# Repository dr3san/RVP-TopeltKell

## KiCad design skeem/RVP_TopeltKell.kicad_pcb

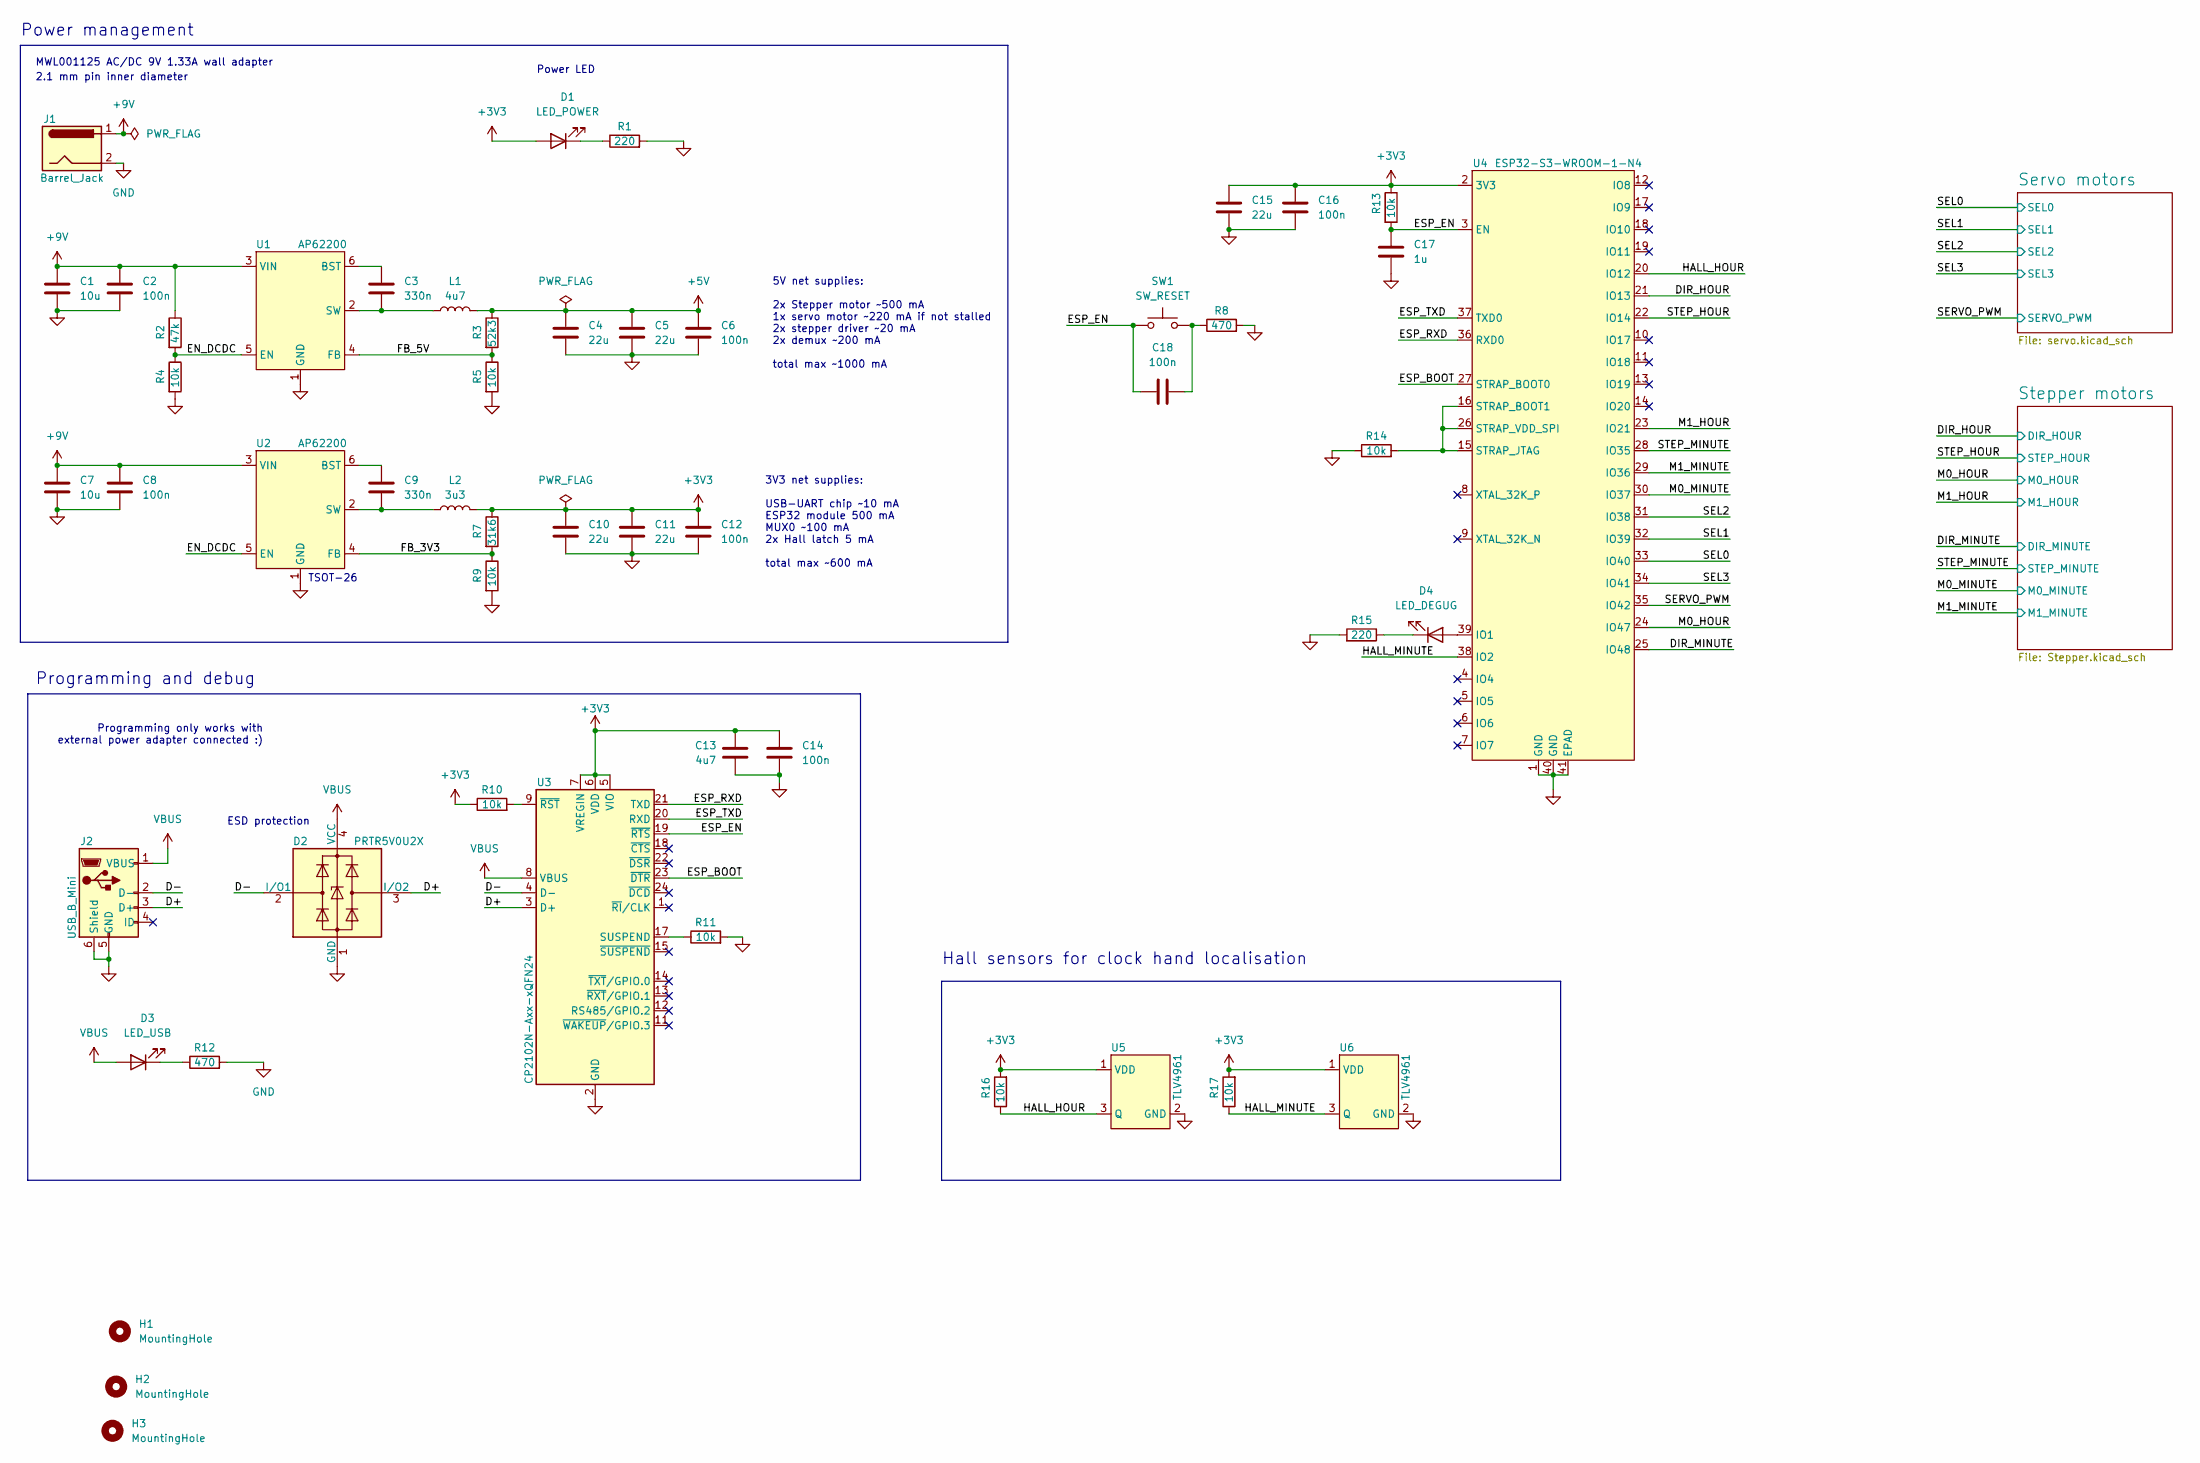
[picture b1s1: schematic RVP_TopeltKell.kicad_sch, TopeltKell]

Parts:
C1, C7: 10u; C_0805_2012Metric_Pad1.18x1.45mm_HandSolder
C2, C6, C8, C12, C14, C16, C18: 100n; C_0603_1608Metric_Pad1.08x0.95mm_HandSolder
C3, C9: 330n; C_0603_1608Metric_Pad1.08x0.95mm_HandSolder
C4, C5, C10, C11, C15: 22u; C_1206_3216Metric_Pad1.33x1.80mm_HandSolder
C13: 4u7; C_0805_2012Metric_Pad1.18x1.45mm_HandSolder
C17: 1u; C_0805_2012Metric_Pad1.18x1.45mm_HandSolder
D1: LED_POWER; LED_0603_1608Metric_Pad1.05x0.95mm_HandSolder
D2: PRTR5V0U2X; SOT-143
D3: LED_USB; LED_0603_1608Metric_Pad1.05x0.95mm_HandSolder
D4: LED_DEGUG; LED_0603_1608Metric_Pad1.05x0.95mm_HandSolder
H1, H2, H3: MountingHole; MountingHole_3.2mm_M3
J1: Barrel_Jack; BarrelJack_CLIFF_FC681465S_SMT_Horizontal
J2: USB_B_Mini; USB_Mini_B
L1: 4u7; L_Wuerth_WE-PD-Typ-7345
L2: 3u3; L_7.3x7.3_H3.5
R1, R15: 220; R_0603_1608Metric_Pad0.98x0.95mm_HandSolder
R2: 47k; R_0603_1608Metric_Pad0.98x0.95mm_HandSolder
R3: 52k3; R_0603_1608Metric_Pad0.98x0.95mm_HandSolder
R4, R5, R9, R10, R11, R13, R14, R16, R17: 10k; R_0603_1608Metric_Pad0.98x0.95mm_HandSolder
R7: 31k6; R_0603_1608Metric_Pad0.98x0.95mm_HandSolder
R8, R12: 470; R_0603_1608Metric_Pad0.98x0.95mm_HandSolder
SW1: SW_RESET; SW_SPST_EVQQ2
U1, U2: AP62200; TSOT26
U3: CP2102N-Axx-xQFN24; QFN-24-1EP_4x4mm_P0.5mm_EP2.6x2.6mm
U4: ESP32-S3-WROOM-1-N4; ESP32-S3-WROOM-1
U5, U6: TLV4961; TO-92S

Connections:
+5V: C4.1, C5.1, C6.2, L1.2, R3.1; also elsewhere on the board
+9V: C1.1, C2.2, C7.1, C8.2, J1.1, R2.1, U1.3 (VIN), U2.3 (VIN); also elsewhere on the board
/D+: D2.3 (I/O2), J2.3 (D+), U3.3 (D+)
/D-: D2.2 (I/O1), J2.2 (D-), U3.4 (D-)
/DIR_HOUR: U4.21 (IO13); also elsewhere on the board
/DIR_MINUTE: U4.25 (IO48); also elsewhere on the board
/EN_DCDC: R2.2, R4.1, U1.5 (EN), U2.5 (EN)
/ESP_BOOT: U3.23 (~DTR), U4.27 (STRAP_BOOT0)
/ESP_EN: C17.1, C18.2, R13.2, SW1.2, U3.19 (~RTS), U4.3 (EN)
/ESP_RXD: U3.21 (TXD), U4.36 (RXD0)
/ESP_TXD: U3.20 (RXD), U4.37 (TXD0)
/FB_3V3: R7.2, R9.1, U2.4 (FB)
/FB_5V: R3.2, R5.1, U1.4 (FB)
/HALL_HOUR: R16.1, U4.20 (IO12), U5.3 (Q)
/HALL_MINUTE: R17.1, U4.38 (IO2), U6.3 (Q)
/M0_HOUR: U4.24 (IO47); also elsewhere on the board
/M0_MINUTE: U4.30 (IO37); also elsewhere on the board
/M1_HOUR: U4.23 (IO21); also elsewhere on the board
/M1_MINUTE: U4.29 (IO36); also elsewhere on the board
/SEL0: U4.33 (IO40); also elsewhere on the board
/SEL1: U4.32 (IO39); also elsewhere on the board
/SEL2: U4.31 (IO38); also elsewhere on the board
/SEL3: U4.34 (IO41); also elsewhere on the board
/SERVO_PWM: U4.35 (IO42); also elsewhere on the board
/STEP_HOUR: U4.22 (IO14); also elsewhere on the board
/STEP_MINUTE: U4.28 (IO35); also elsewhere on the board
GND: C1.2, C2.1, C4.2, C5.2, C6.1, C7.2, C8.1, C10.2, C11.2, C12.1, C13.1, C14.2, C15.2, C16.2, C17.2, D2.1 (GND), J1.2, J2.5 (GND), J2.6 (Shield), R1.2, R4.2, R5.2, R8.2, R9.2, R11.2, R12.2, R14.1, R15.2, U1.1 (GND), U2.1 (GND), U3.2 (GND), U3.25 (GND), U4.1 (GND), U4.40 (GND), U4.41 (EPAD), U5.2 (GND), U6.2 (GND); also elsewhere on the board
unnamed: C18.1, R8.1, SW1.1
unnamed: D1.1 (K), R1.1
unnamed: D3.1 (K), R12.1
unnamed: D4.2 (A), U4.39 (IO1)
unnamed: D4.1 (K), R15.1
unnamed: C3.2, U1.6 (BST)
unnamed: C3.1, L1.1, U1.2 (SW)
unnamed: C9.2, U2.6 (BST)
unnamed: C9.1, L2.1, U2.2 (SW)
unnamed: R11.1, U3.17 (SUSPEND)
unnamed: R10.2, U3.9 (~RST)
unnamed: R14.2, U4.15 (STRAP_JTAG), U4.16 (STRAP_BOOT1), U4.26 (STRAP_VDD_SPI)
VBUS: D2.4 (VCC), D3.2 (A), J2.1 (VBUS), U3.8 (VBUS)

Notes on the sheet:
ESD protection
Programming only works with external power adapter connected :)
2.1 mm pin inner diameter
MWL001125 AC/DC 9V 1.33A wall adapter
Programming and debug
TSOT-26
3V3 net supplies: USB-UART chip ~10 mA ESP32 module 500 mA MUX0 ~100 mA 2x Hall latch 5 mA total max ~600 mA
5V net supplies: 2x Stepper motor ~500 mA 1x servo motor ~220 mA if not stalled 2x stepper driver ~20 mA 2x demux ~200 mA total max ~1000 mA
Hall sensors for clock hand localisation
Power LED
Power management

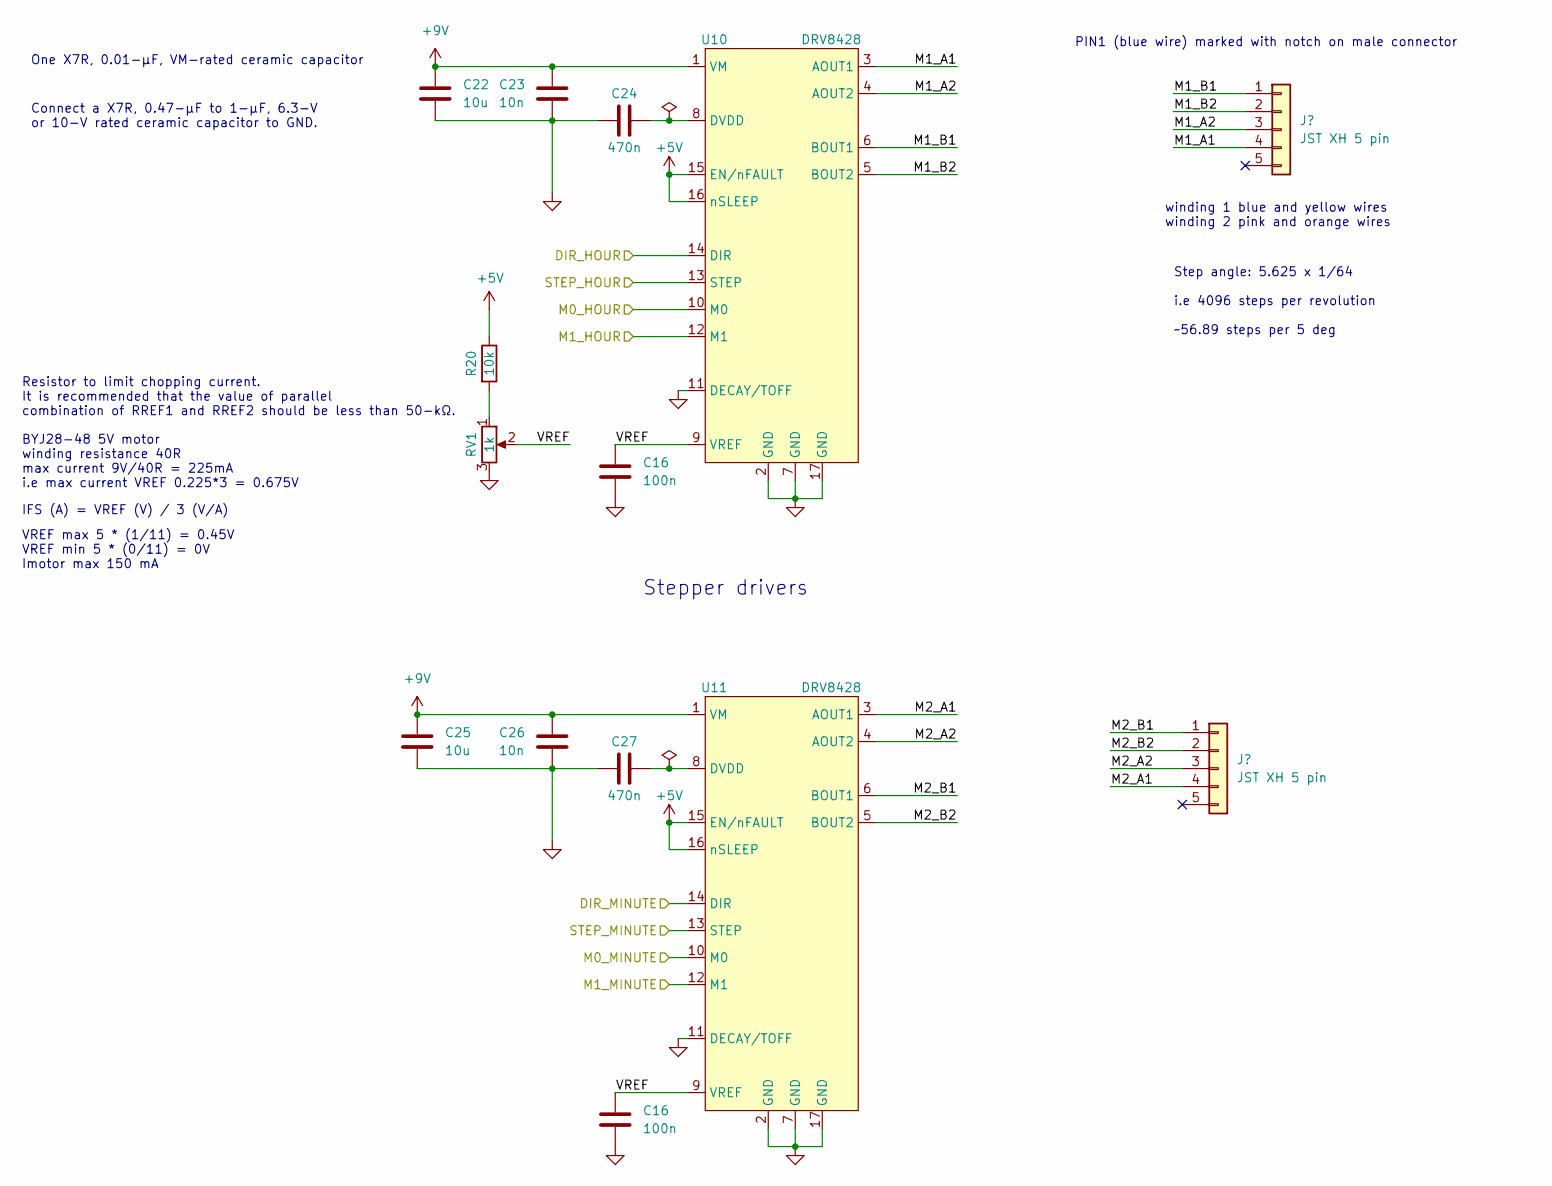
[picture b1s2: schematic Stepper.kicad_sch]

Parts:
C16: 100n; C_0603_1608Metric_Pad1.08x0.95mm_HandSolder
C22, C25: 10u; C_0805_2012Metric_Pad1.18x1.45mm_HandSolder
C23, C26: 10n; C_0603_1608Metric_Pad1.08x0.95mm_HandSolder
C24, C27: 470n; C_0603_1608Metric_Pad1.08x0.95mm_HandSolder
J15, J16: JST XH 5 pin; JST_XH_B5B-XH-A_1x05_P2.50mm_Vertical
R20: 10k; R_0603_1608Metric_Pad0.98x0.95mm_HandSolder
RV1: 1k; Potentiometer_Bourns_3386P_Vertical
U10, U11: DRV8428; HTSSOP-16-1EP_4.4x5mm_P0.65mm_EP3x3mm

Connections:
+5V: R20.1, U10.15 (EN/nFAULT), U10.16 (nSLEEP), U11.15 (EN/nFAULT), U11.16 (nSLEEP); also elsewhere on the board
+9V: C22.1, C23.2, C25.1, C26.2, U10.1 (VM), U11.1 (VM); also elsewhere on the board
/DIR_HOUR: U10.14 (DIR); also elsewhere on the board
/DIR_MINUTE: U11.14 (DIR); also elsewhere on the board
/M0_HOUR: U10.10 (M0); also elsewhere on the board
/M0_MINUTE: U11.10 (M0); also elsewhere on the board
/M1_HOUR: U10.12 (M1); also elsewhere on the board
/M1_MINUTE: U11.12 (M1); also elsewhere on the board
/STEP_HOUR: U10.13 (STEP); also elsewhere on the board
/STEP_MINUTE: U11.13 (STEP); also elsewhere on the board
/Stepper motors/M1_A1: J15.4, U10.3 (AOUT1)
/Stepper motors/M1_A2: J15.3, U10.4 (AOUT2)
/Stepper motors/M1_B1: J15.1, U10.6 (BOUT1)
/Stepper motors/M1_B2: J15.2, U10.5 (BOUT2)
/Stepper motors/M2_A1: J16.4, U11.3 (AOUT1)
/Stepper motors/M2_A2: J16.3, U11.4 (AOUT2)
/Stepper motors/M2_B1: J16.1, U11.6 (BOUT1)
/Stepper motors/M2_B2: J16.2, U11.5 (BOUT2)
GND: C16.2, C22.2, C23.1, C24.1, C25.2, C26.1, C27.1, RV1.3, U10.2 (GND), U10.7 (GND), U10.11 (DECAY/TOFF), U10.17 (GND), U11.2 (GND), U11.7 (GND), U11.11 (DECAY/TOFF), U11.17 (GND); also elsewhere on the board
unnamed: R20.2, RV1.1
unnamed: C24.2, U10.8 (DVDD)
unnamed: C27.2, U11.8 (DVDD)

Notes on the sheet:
Step angle: 5.625 x 1/64 i.e 4096 steps per revolution ~56.89 steps per 5 deg
Resistor to limit chopping current. It is recommended that the value of parallel combination of RREF1 and RREF2 should be less than 50-kΩ.
Connect a X7R, 0.47-μF to 1-μF, 6.3-V or 10-V rated ceramic capacitor to GND.
VREF max 5 * (1/11) = 0.45V VREF min 5 * (0/11) = 0V Imotor max 150 mA
One X7R, 0.01-μF, VM-rated ceramic capacitor
IFS (A) = VREF (V) / 3 (V/A)
PIN1 (blue wire) marked with notch on male connector
Stepper drivers
BYJ28-48 5V motor winding resistance 40R max current 9V/40R = 225mA i.e max current VREF 0.225*3 = 0.675V
winding 1 blue and yellow wires winding 2 pink and orange wires

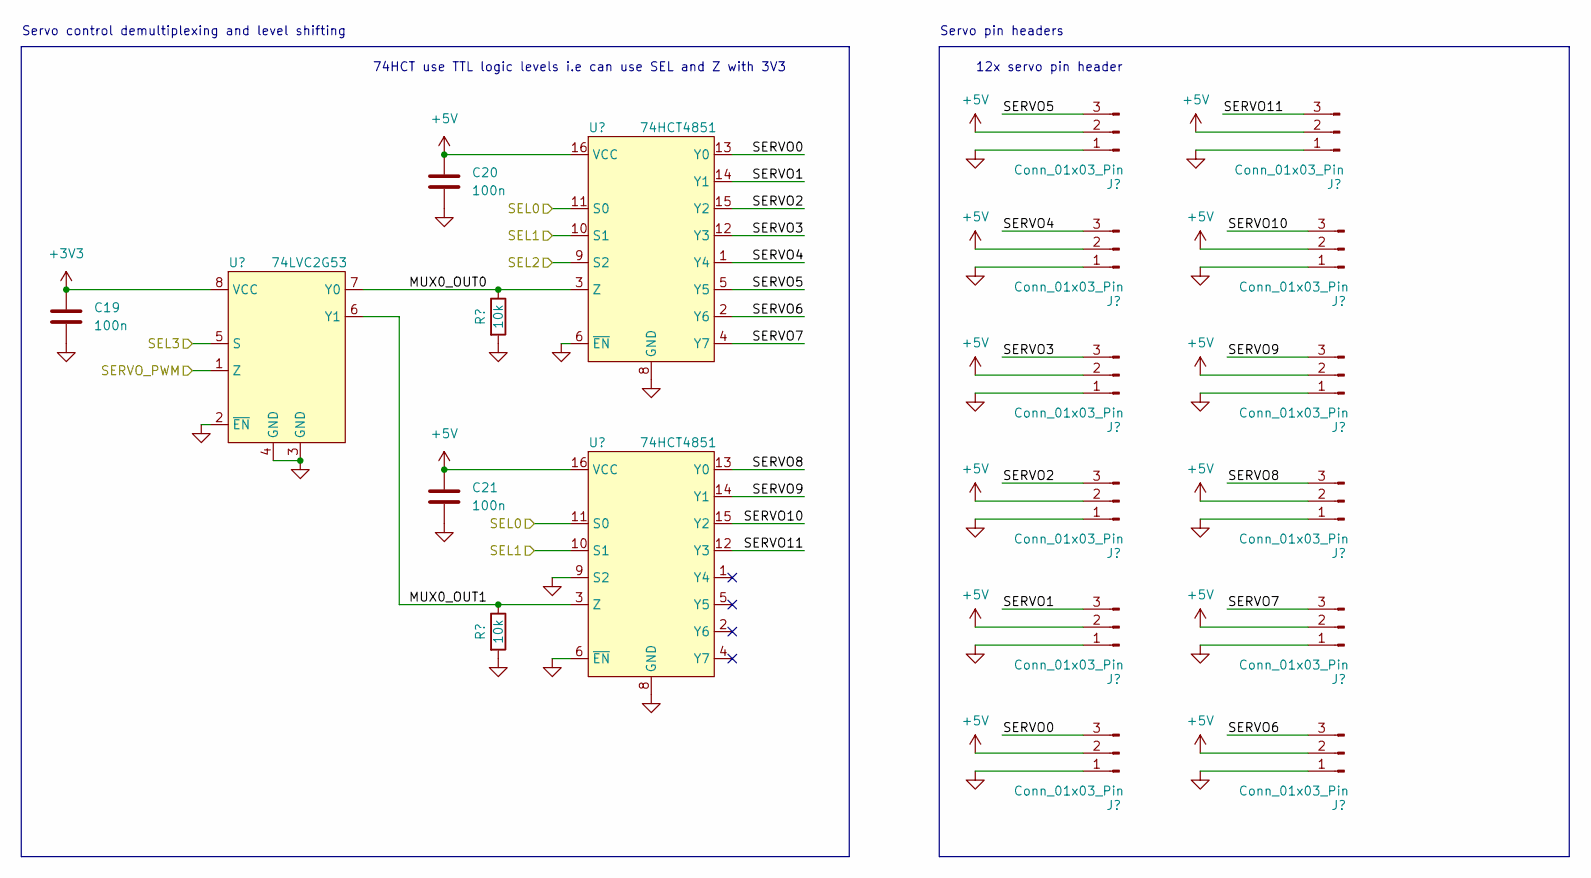
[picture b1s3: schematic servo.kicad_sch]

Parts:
C19, C20, C21: 100n; C_0603_1608Metric_Pad1.08x0.95mm_HandSolder
J3, J4, J5, J6, J7, J8, J9, J10, J11, J12, J13, J14: Conn_01x03_Pin; PinHeader_1x03_P2.54mm_Vertical
R18, R19: 10k; R_0603_1608Metric_Pad0.98x0.95mm_HandSolder
U7: 74LVC2G53; TSSOP-8_3x3mm_P0.65mm
U8, U9: 74HCT4851; SO-16_3.9x9.9mm_P1.27mm

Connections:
+5V: C20.1, C21.1, J3.2, J4.2, J5.2, J6.2, J7.2, J8.2, J9.2, J10.2, J11.2, J12.2, J13.2, J14.2, U8.16 (VCC), U9.16 (VCC); also elsewhere on the board
/SEL0: U8.11 (S0), U9.11 (S0); also elsewhere on the board
/SEL1: U8.10 (S1), U9.10 (S1); also elsewhere on the board
/SEL2: U8.9 (S2); also elsewhere on the board
/SEL3: U7.5 (S); also elsewhere on the board
/SERVO_PWM: U7.1 (Z); also elsewhere on the board
/Servo motors/MUX0_OUT0: R18.1, U7.7 (Y0), U8.3 (Z)
/Servo motors/MUX0_OUT1: R19.1, U7.6 (Y1), U9.3 (Z)
/Servo motors/SERVO0: J3.3, U8.13 (Y0)
/Servo motors/SERVO1: J4.3, U8.14 (Y1)
/Servo motors/SERVO2: J5.3, U8.15 (Y2)
/Servo motors/SERVO3: J6.3, U8.12 (Y3)
/Servo motors/SERVO4: J7.3, U8.1 (Y4)
/Servo motors/SERVO5: J8.3, U8.5 (Y5)
/Servo motors/SERVO6: J9.3, U8.2 (Y6)
/Servo motors/SERVO7: J10.3, U8.4 (Y7)
/Servo motors/SERVO8: J11.3, U9.13 (Y0)
/Servo motors/SERVO9: J12.3, U9.14 (Y1)
/Servo motors/SERVO10: J13.3, U9.15 (Y2)
/Servo motors/SERVO11: J14.3, U9.12 (Y3)
GND: C19.2, C20.2, C21.2, J3.1, J4.1, J5.1, J6.1, J7.1, J8.1, J9.1, J10.1, J11.1, J12.1, J13.1, J14.1, R18.2, R19.2, U7.2 (~EN), U7.3 (GND), U7.4 (GND), U8.6 (~EN), U8.8 (GND), U9.6 (~EN), U9.8 (GND), U9.9 (S2); also elsewhere on the board

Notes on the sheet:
12x servo pin header
74HCT use TTL logic levels i.e can use SEL and Z with 3V3
Servo pin headers
Servo control demultiplexing and level shifting

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
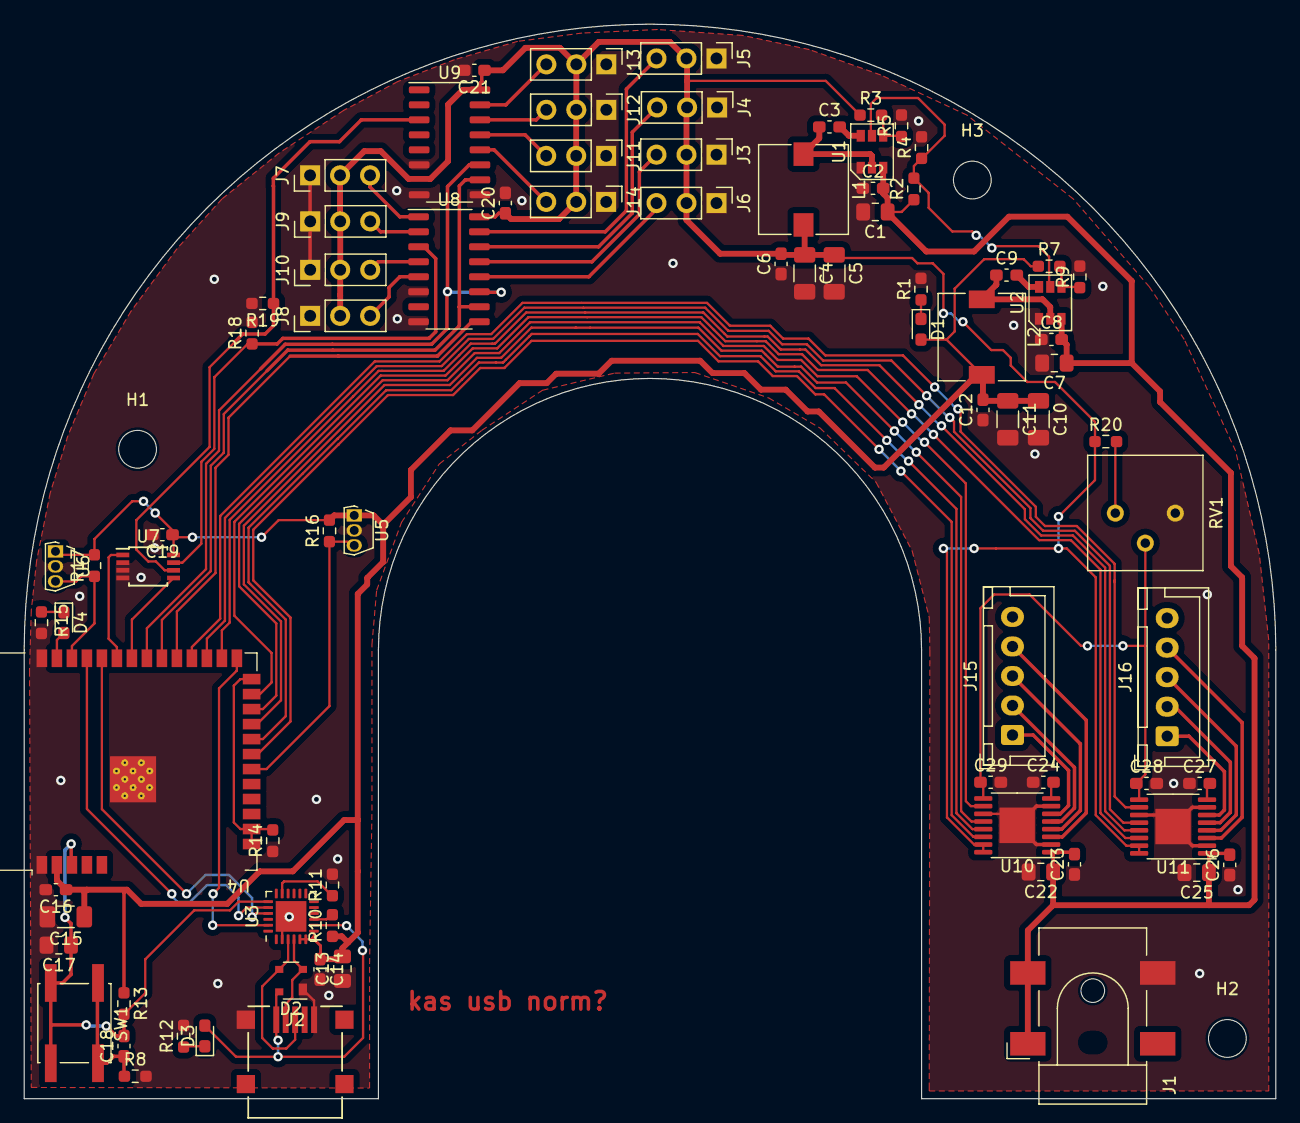
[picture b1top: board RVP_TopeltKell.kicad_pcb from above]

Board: 2 copper layers, 106.0 x 91.0 mm, 86 parts (0 on the bottom side), 67 nets.

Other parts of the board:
C28, C29: 100n; C_0603_1608Metric_Pad1.08x0.95mm_HandSolder

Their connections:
GND: C28.2, C29.2; also elsewhere on the board

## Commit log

2023-10-14 Lisatud Kicad projekt
2023-10-18 nibin-nabin skeem
2023-10-18 skem
2023-10-20 skeem edeneb
2023-10-22 Hall Sensor
2023-10-24 power mgmt
2023-10-24 arendus
2023-10-27 nu and impruvd
2023-10-31 veel skeemi
2023-11-01 skeem
2023-11-13 pcb comp placement draft
2023-11-13 3d models for pcb
2023-11-19 natuke pcbd
2023-11-20 ruuditud v1
2023-11-21 pisibi valma???
